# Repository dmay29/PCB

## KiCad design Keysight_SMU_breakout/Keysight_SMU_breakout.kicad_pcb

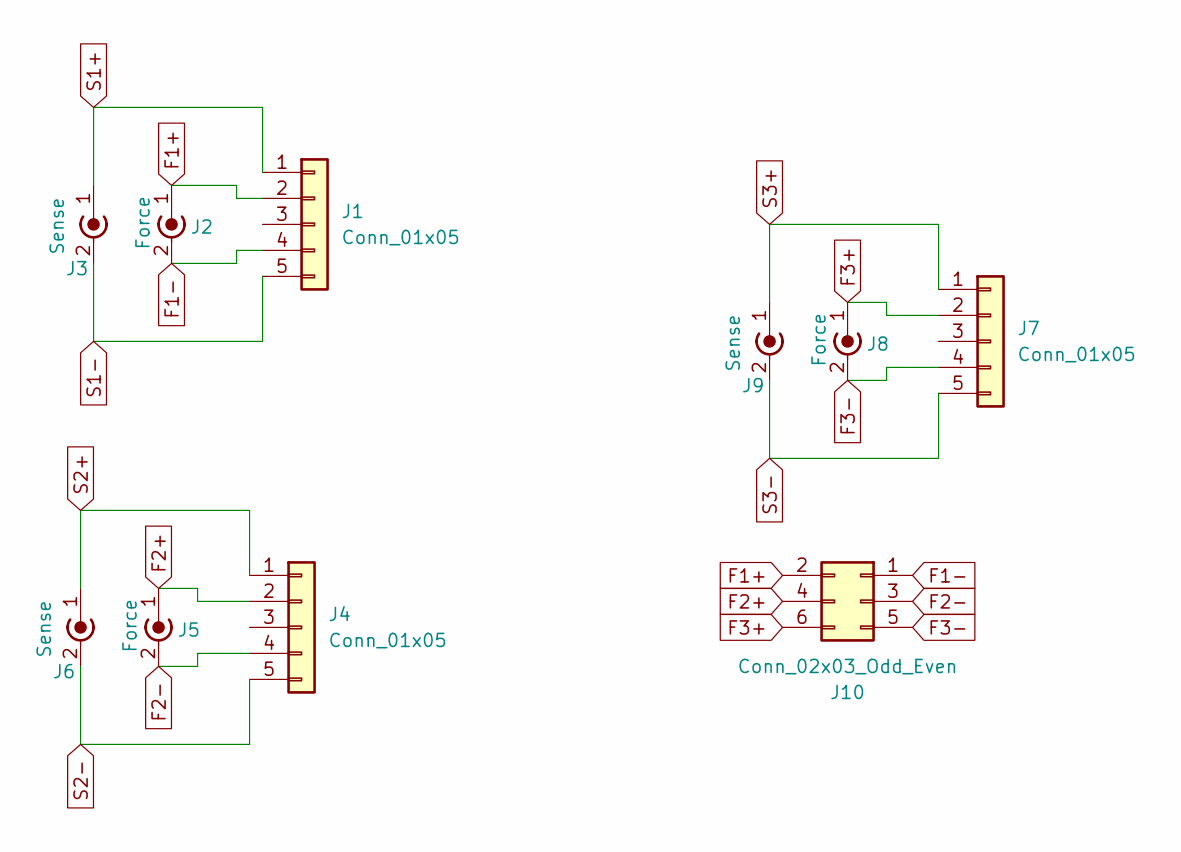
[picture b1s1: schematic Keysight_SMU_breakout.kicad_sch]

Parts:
J1, J4, J7: Conn_01x05; TerminalBlock_Phoenix_MKDS-1-5-3.81_1x05_P3.81mm_Horizontal
J2, J5, J8: Force; BNC_TEConnectivity_1478204_Vertical
J3, J6, J9: Sense; BNC_TEConnectivity_1478204_Vertical
J10: Conn_02x03_Odd_Even; PinHeader_2x03_P2.54mm_Vertical

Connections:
F1+: J1.2, J2.1 (In), J10.2
F1-: J1.4, J2.2 (Ext), J10.1
F2+: J4.2, J5.1 (In), J10.4
F2-: J4.4, J5.2 (Ext), J10.3
F3+: J7.2, J8.1 (In), J10.6
F3-: J7.4, J8.2 (Ext), J10.5
S1+: J1.1, J3.1 (In)
S1-: J1.5, J3.2 (Ext)
S2+: J4.1, J6.1 (In)
S2-: J4.5, J6.2 (Ext)
S3+: J7.1, J9.1 (In)
S3-: J7.5, J9.2 (Ext)

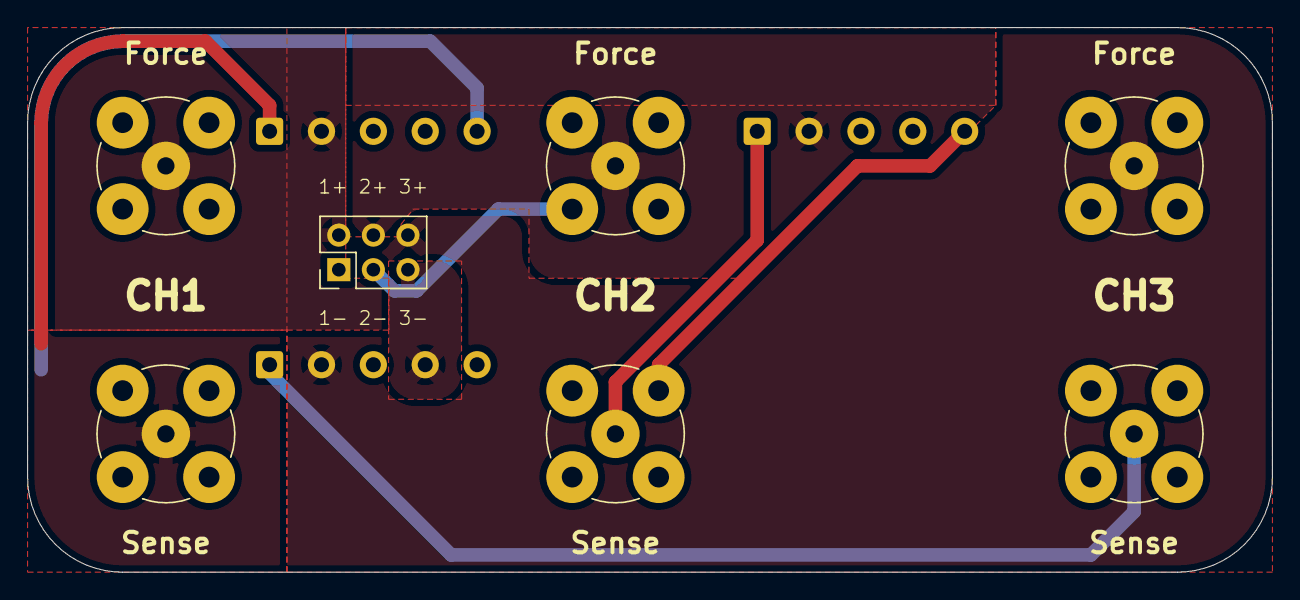
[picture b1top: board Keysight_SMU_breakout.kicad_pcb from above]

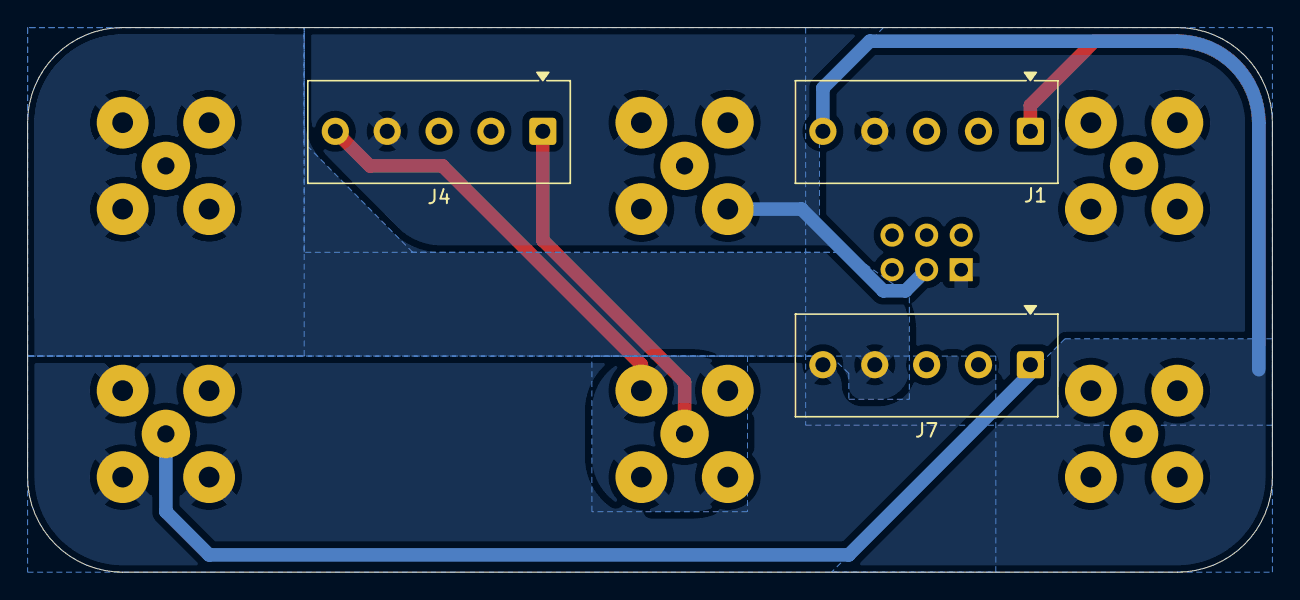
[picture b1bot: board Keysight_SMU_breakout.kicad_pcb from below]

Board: 2 copper layers, 91.4 x 40.0 mm, 10 parts (3 on the bottom side), 12 nets.

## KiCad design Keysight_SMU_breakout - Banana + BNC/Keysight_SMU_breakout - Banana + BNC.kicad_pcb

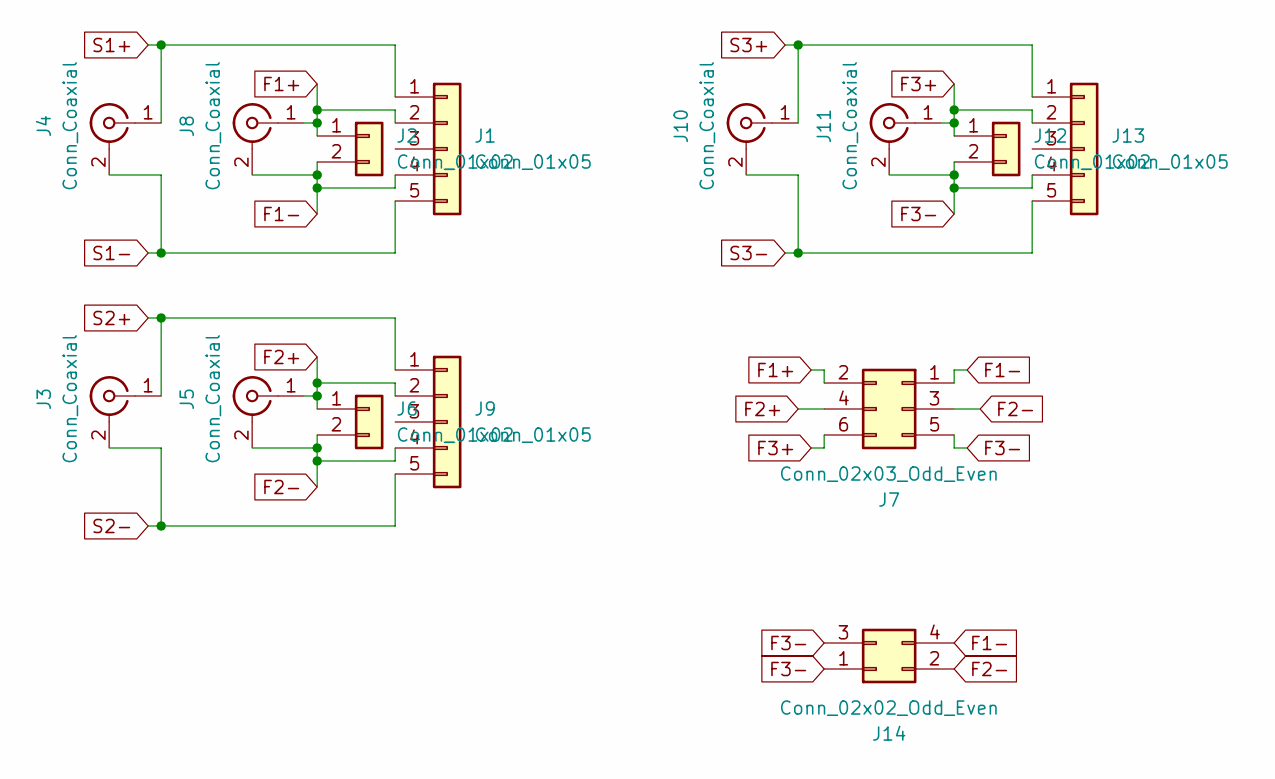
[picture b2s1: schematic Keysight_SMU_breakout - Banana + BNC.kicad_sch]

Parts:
J1, J9, J13: Conn_01x05; TerminalBlock_Phoenix_MKDS-1-5-3.81_1x05_P3.81mm_Horizontal
J2, J6, J12: Conn_01x02; Dual Banana
J3, J4, J5, J8, J10, J11: Conn_Coaxial; BNC_TEConnectivity_1478204_Vertical
J7: Conn_02x03_Odd_Even; PinHeader_2x03_P2.54mm_Vertical
J14: Conn_02x02_Odd_Even; PinHeader_2x02_P2.54mm_Vertical

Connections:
F1+: J1.2, J2.1, J7.2, J8.1 (In)
F1-: J1.4, J2.2, J7.1, J8.2 (Ext), J14.4
F2+: J5.1 (In), J6.1, J7.4, J9.2
F2-: J5.2 (Ext), J6.2, J7.3, J9.4, J14.2
F3+: J7.6, J11.1 (In), J12.1, J13.2
F3-: J7.5, J11.2 (Ext), J12.2, J13.4, J14.1, J14.3
S1+: J1.1, J4.1 (In)
S1-: J1.5, J4.2 (Ext)
S2+: J3.1 (In), J9.1
S2-: J3.2 (Ext), J9.5
S3+: J10.1 (In), J13.1
S3-: J10.2 (Ext), J13.5

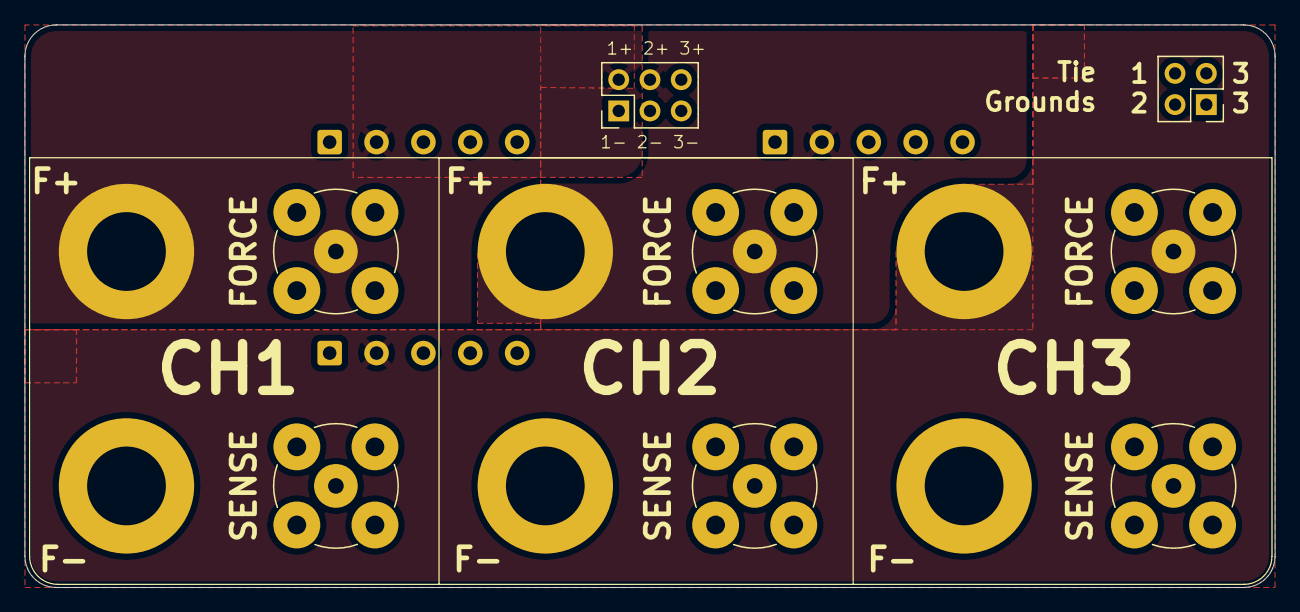
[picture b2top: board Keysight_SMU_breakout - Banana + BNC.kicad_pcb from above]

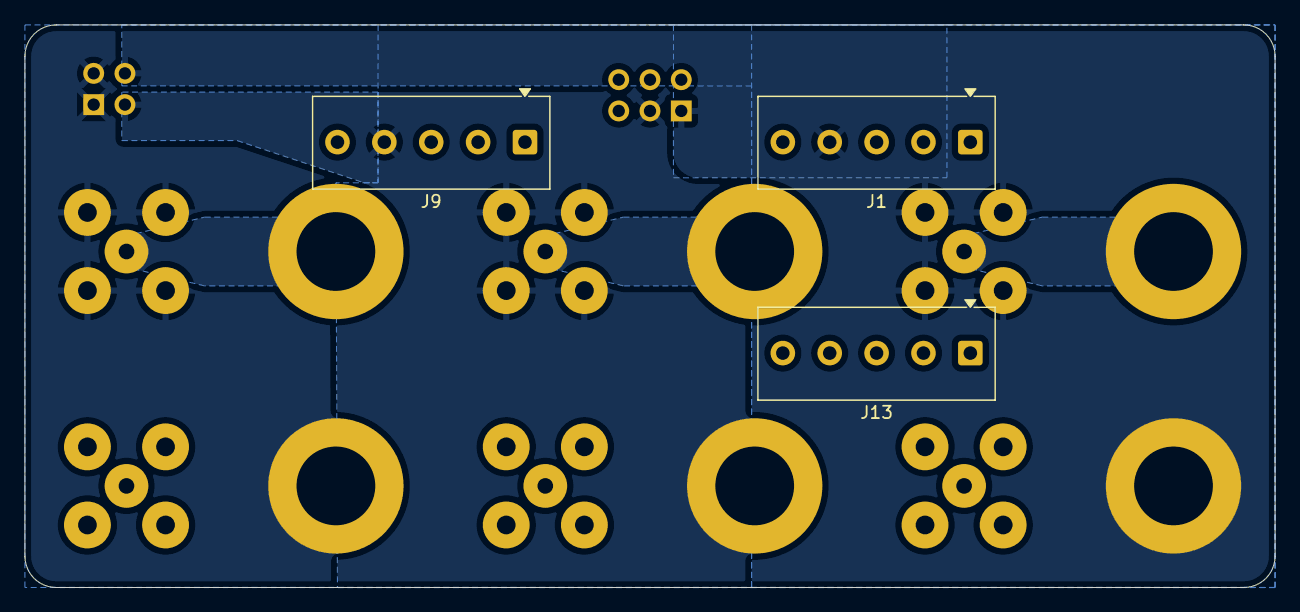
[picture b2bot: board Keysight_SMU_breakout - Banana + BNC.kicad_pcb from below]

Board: 4 copper layers, 101.6 x 45.7 mm, 14 parts (3 on the bottom side), 12 nets.

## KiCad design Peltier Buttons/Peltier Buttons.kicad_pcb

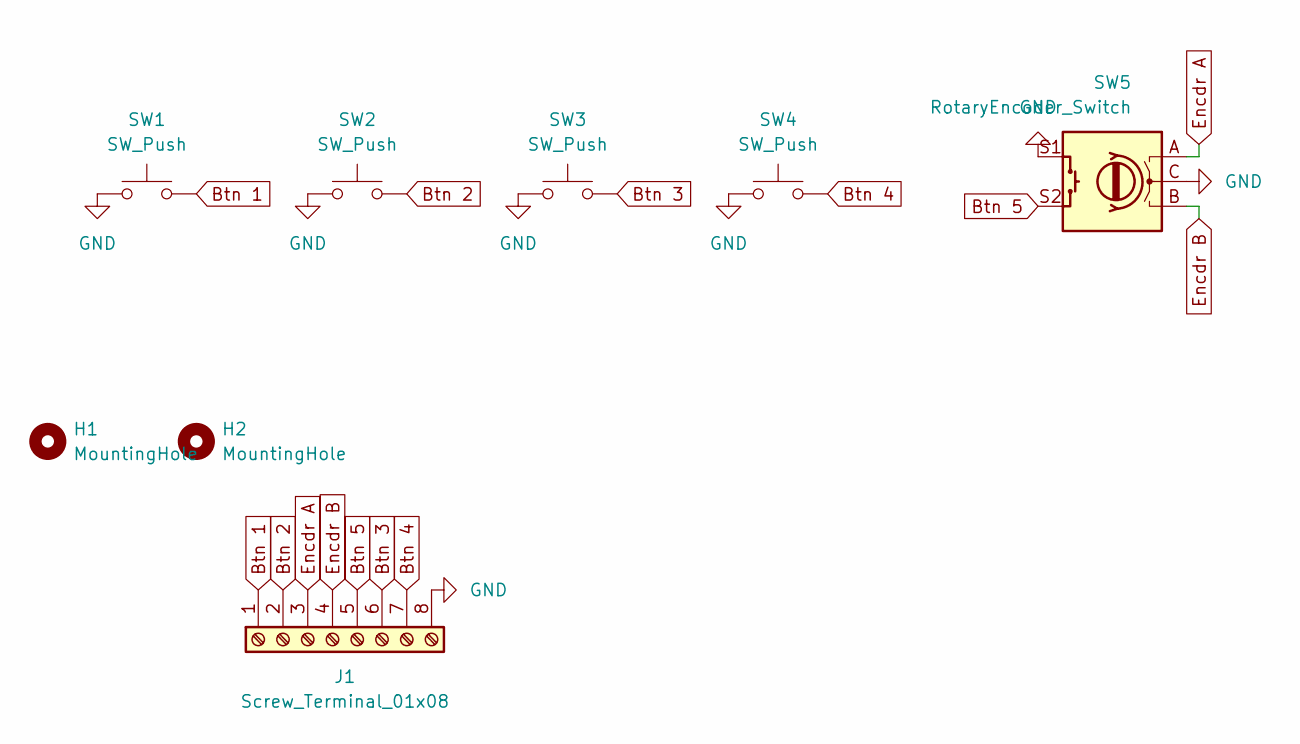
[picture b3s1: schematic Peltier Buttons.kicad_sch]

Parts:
H1, H2: MountingHole; MountingHole_2.7mm_M2.5
J1: Screw_Terminal_01x08; TerminalBlock_TE_282834-8_1x08_P2.54mm_Horizontal
SW1, SW2, SW3, SW4: SW_Push; SW_SPST_Omron_B3F-50xx
SW5: RotaryEncoder_Switch; RotaryEncoder_Bourns_Vertical_PEC12R-3x17F-Sxxxx

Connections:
Btn 1: J1.1, SW1.2
Btn 2: J1.2, SW2.2
Btn 3: J1.6, SW3.2
Btn 4: J1.7, SW4.2
Btn 5: J1.5, SW5.S2
Encdr A: J1.3, SW5.A
Encdr B: J1.4, SW5.B
GND: J1.8, SW1.1, SW2.1, SW3.1, SW4.1, SW5.C, SW5.S1

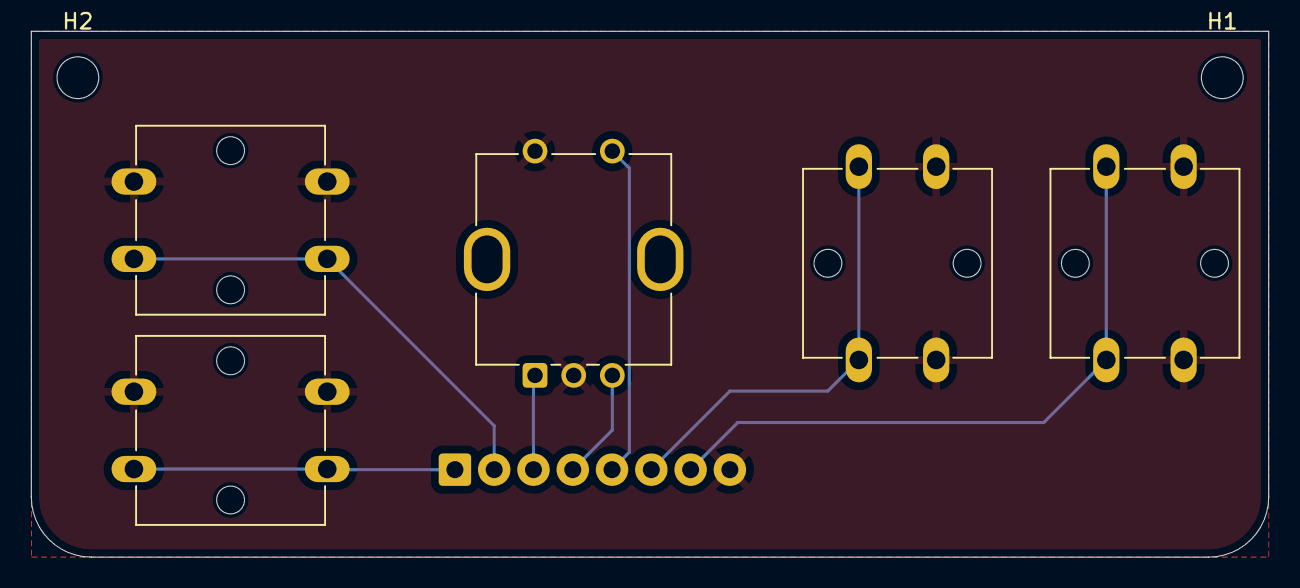
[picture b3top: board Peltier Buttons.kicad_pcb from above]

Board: 2 copper layers, 80.0 x 34.0 mm, 8 parts (1 on the bottom side), 8 nets.

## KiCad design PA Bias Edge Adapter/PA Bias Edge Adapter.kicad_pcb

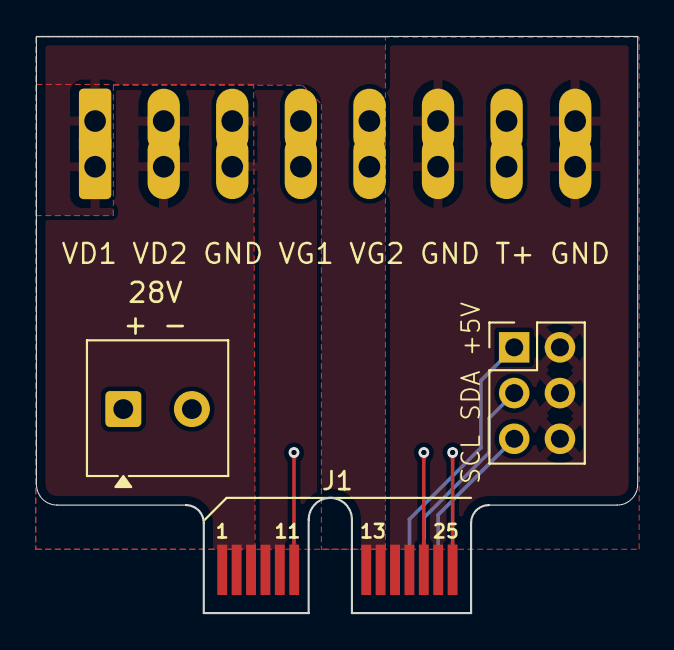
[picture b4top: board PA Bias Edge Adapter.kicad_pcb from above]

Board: 4 copper layers, 33.3 x 32.0 mm, 4 parts (1 on the bottom side), 10 nets.

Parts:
J1: Conn_02x13_Odd_Even; Samtec_HSEC8-113-X-X-DV_2x13_P0.8mm_Wing_Edge
J2: Screw_Terminal_01x08; PhoenixContact_MC_1,5_8-G-3.81_1x08_P3.81mm_Horizontal_Fema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
J3: Screw_Terminal_01x02; TerminalBlock_Phoenix_MKDS-1-2-3.81_1x02_P3.81mm_Horizontal
J4: Conn_02x03_Odd_Even; PinHeader_2x03_P2.54mm_Vertical

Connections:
+5V: J1.20, J4.1
/28V: J1.2, J1.4, J1.6, J1.8, J3.1
/T+: J1.25, J2.7
/VD1: J1.13, J1.15, J2.1
/VD2: J1.1, J1.3, J1.5, J2.2
/VG1: J1.21, J2.4
/VG2: J1.11, J2.5
GND: J1.7, J1.9, J1.10, J1.12, J1.14, J1.16, J1.17, J1.18, J1.19, J1.23, J1.26, J2.3, J2.6, J2.8, J3.2, J4.2, J4.4, J4.6
SCL: J1.24, J4.5
SDA: J1.22, J4.3

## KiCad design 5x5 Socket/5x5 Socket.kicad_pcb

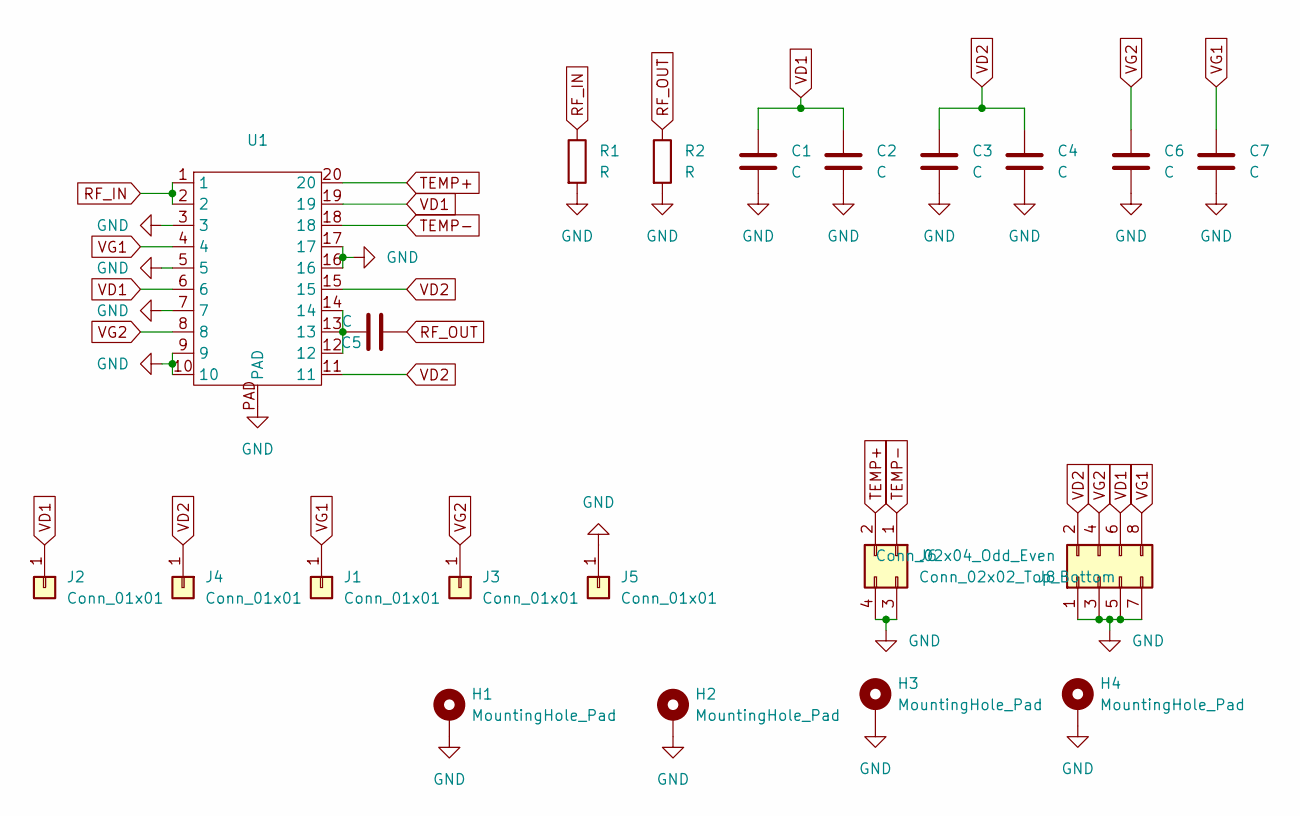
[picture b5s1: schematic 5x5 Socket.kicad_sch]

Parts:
C1, C2, C3, C4, C5, C6, C7: C; C_0603_1608Metric_Pad1.08x0.95mm_HandSolder
H1, H2, H3, H4: MountingHole_Pad; MountingHole_3.2mm_M3_Pad_Via
J1, J2, J3, J4, J5: Conn_01x01; Banana_Cliff_FCR7350Y_S16N-PC_Horizontal
J6: Conn_02x02_Top_Bottom; PinHeader_2x02_P2.54mm_Vertical
J8: Conn_02x04_Odd_Even; PinHeader_2x04_P2.54mm_Vertical
R1, R2: R; R_0603_1608Metric_Pad0.98x0.95mm_HandSolder
U1: 5x5 QFN Socket

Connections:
GND: C1.2, C2.2, C3.2, C4.2, C6.2, C7.2, H1.1, H2.1, H3.1, H4.1, J5.1, J6.3, J6.4, J8.1, J8.3, J8.5, J8.7, R1.2, R2.2, U1.3, U1.5, U1.7, U1.9, U1.10, U1.16, U1.17, U1.PAD
unnamed: C5.1, U1.12, U1.13, U1.14
RF_IN: R1.1, U1.1, U1.2
RF_OUT: C5.2, R2.1
TEMP+: J6.2, U1.20
TEMP-: J6.1, U1.18
VD1: C1.1, C2.1, J2.1, J8.6, U1.6, U1.19
VD2: C3.1, C4.1, J4.1, J8.2, U1.11, U1.15
VG1: C7.1, J1.1, J8.8, U1.4
VG2: C6.1, J3.1, J8.4, U1.8

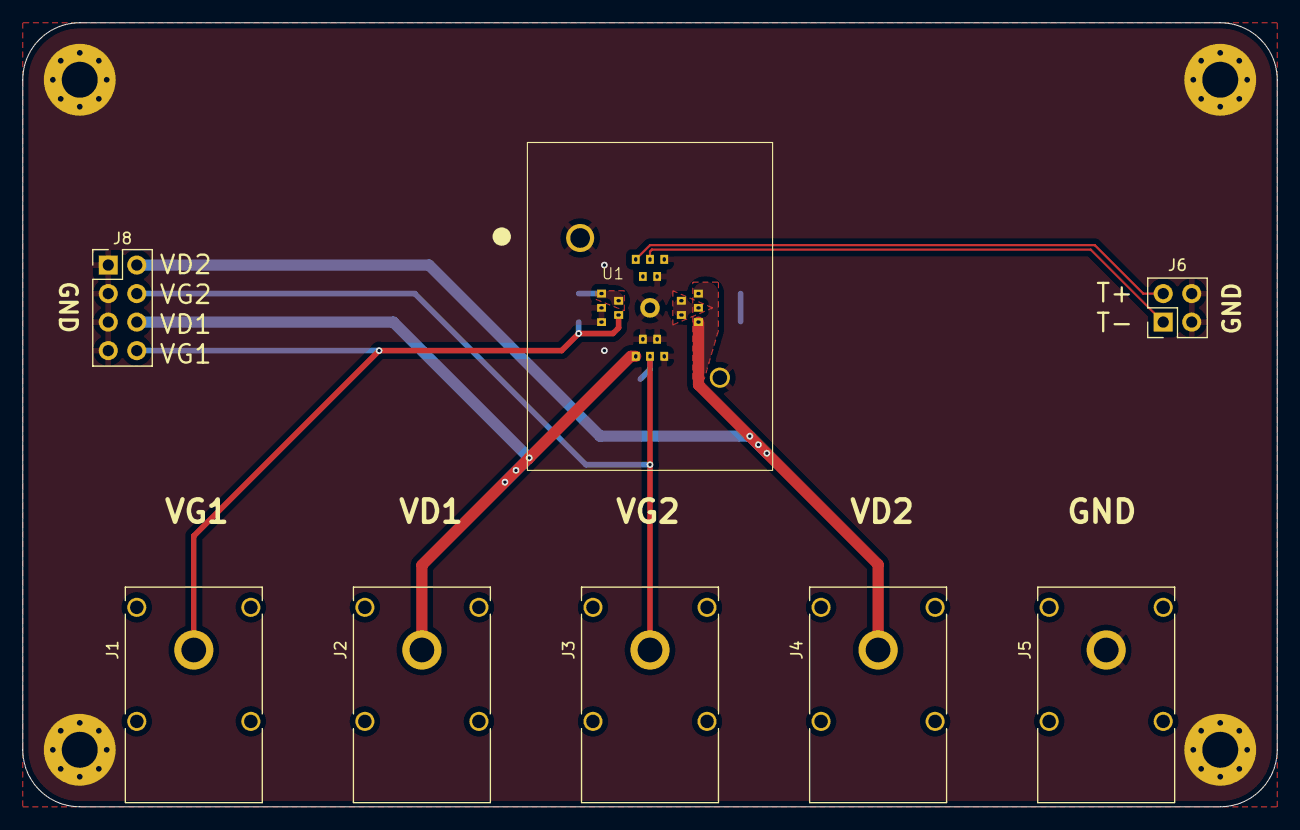
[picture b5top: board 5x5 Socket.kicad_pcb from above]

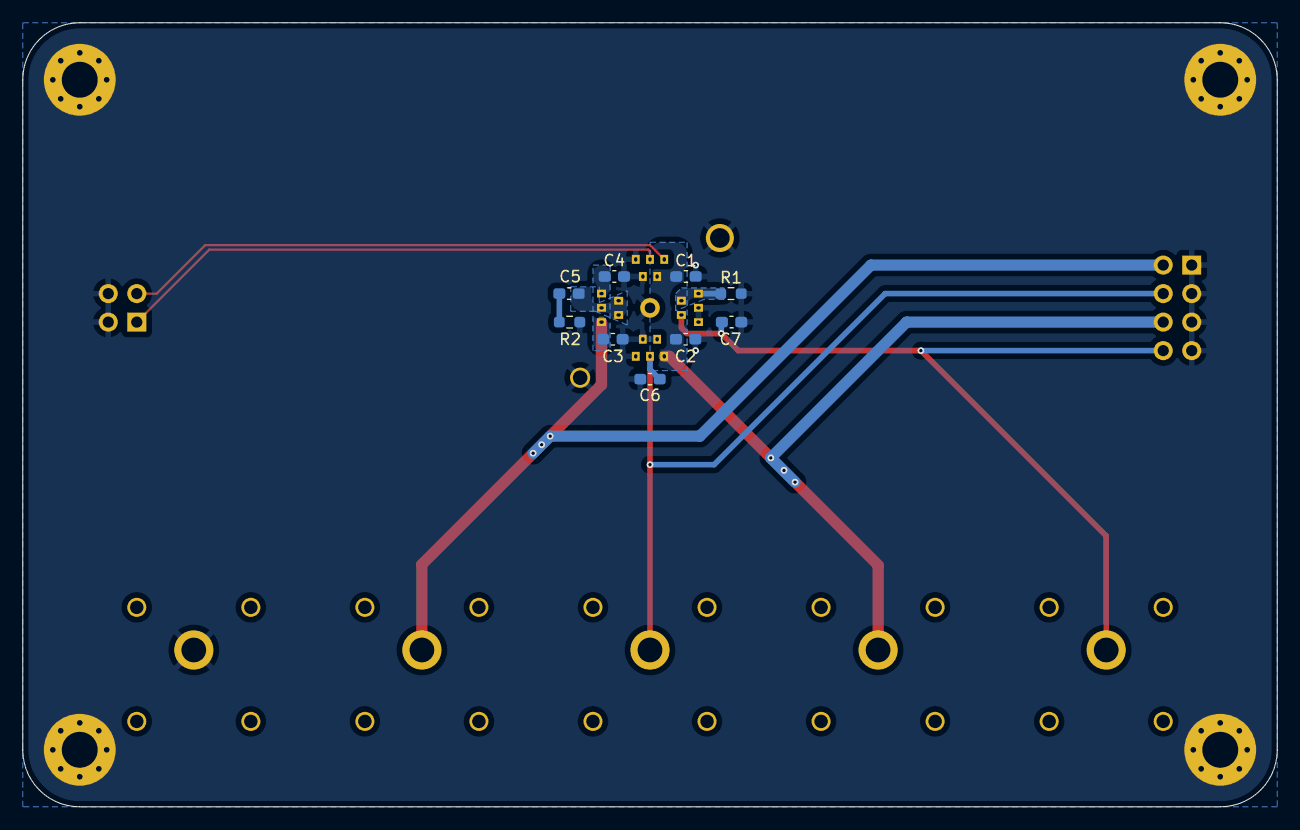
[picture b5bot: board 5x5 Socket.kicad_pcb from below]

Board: 2 copper layers, 111.8 x 69.8 mm, 21 parts (9 on the bottom side), 10 nets.

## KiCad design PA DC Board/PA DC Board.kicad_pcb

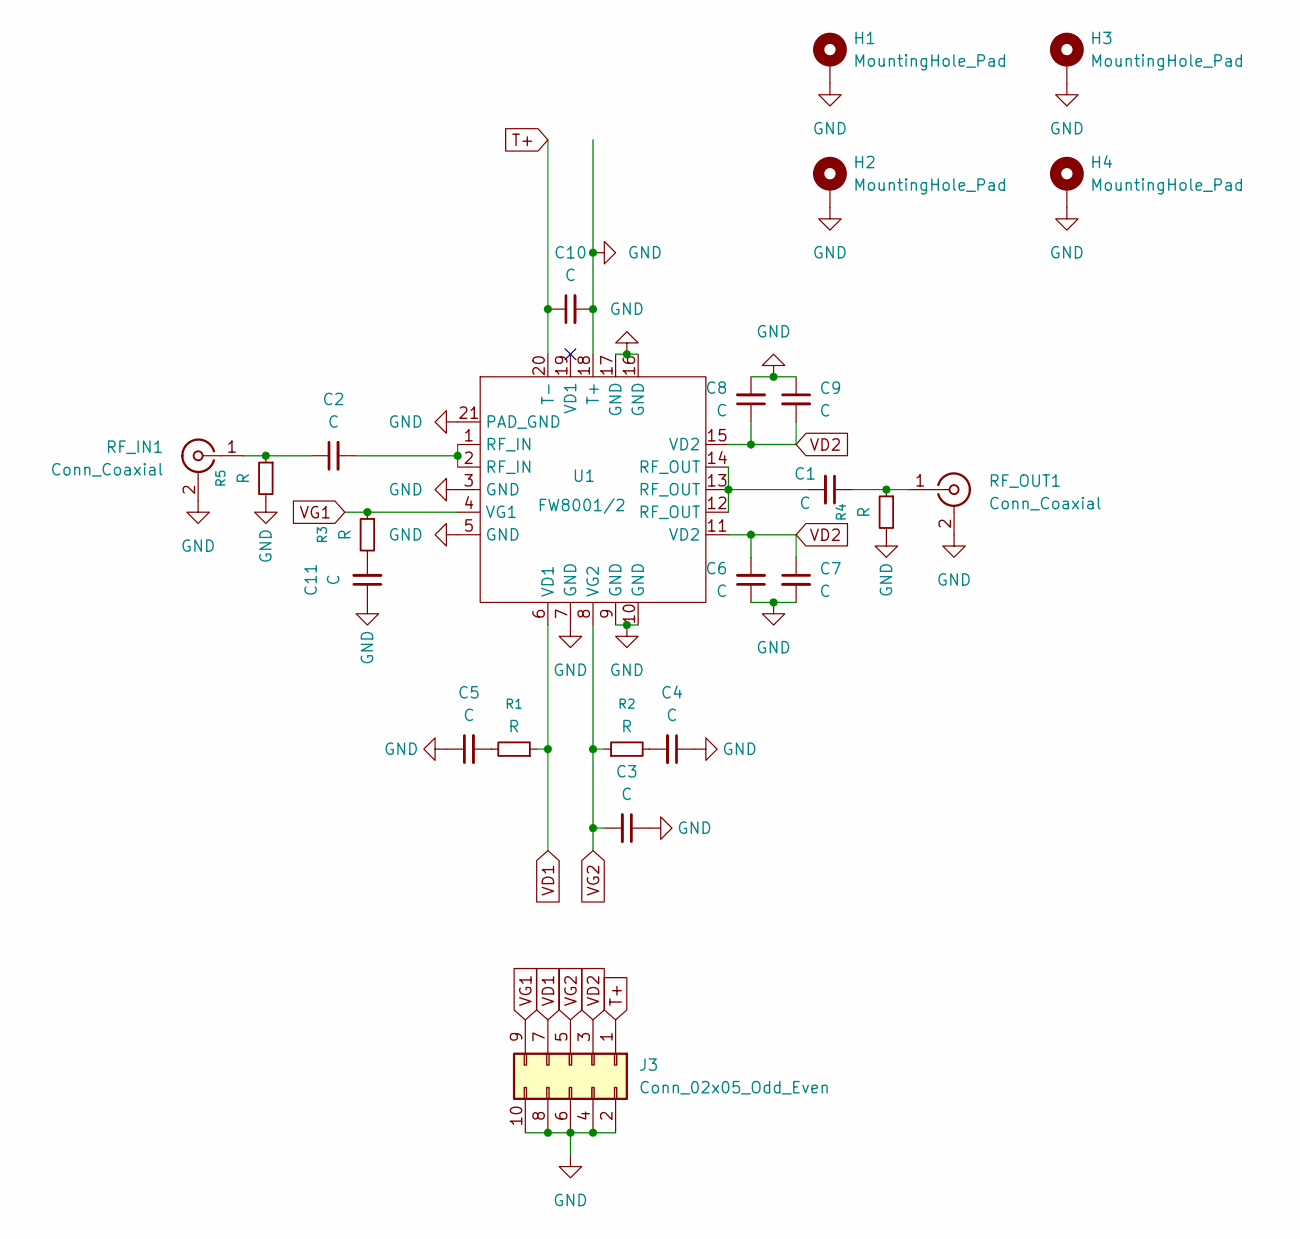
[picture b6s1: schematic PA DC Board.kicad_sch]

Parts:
C1, C2, C3, C4, C5, C10, C11: C; C_0603_1608Metric
C6, C7, C8, C9: C; C_1210_3225Metric
H1, H2, H3, H4: MountingHole_Pad; MountingHole_2.7mm_M2.5_DIN965_Pad_TopBottom
J3: Conn_02x05_Odd_Even; PinHeader_2x05_P2.54mm_Vertical_SMD
R1, R2, R3, R4, R5: R; R_0603_1608Metric
RF_IN1: Conn_Coaxial; SMA_Amphenol_132134-10_Vertical
RF_OUT1: Conn_Coaxial; SMA_Amphenol_132134-10_Vertical
U1: FW8001/2; QFN-20-1EP_5x5mm_P0.65mm_EP3.35x3.35mm

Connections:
GND: C3.1, C4.1, C5.1, C6.1, C7.2, C8.2, C9.1, C10.2, C11.1, H1.1, H2.1, H3.1, H4.1, J3.2, J3.4, J3.6, J3.8, J3.10, R4.2, R5.2, RF_IN1.2 (Ext), RF_OUT1.2 (Ext), U1.3 (GND), U1.5 (GND), U1.7 (GND), U1.9 (GND), U1.10 (GND), U1.16 (GND), U1.17 (GND), U1.18 (T+), U1.21 (PAD_GND)
unnamed: C1.2, U1.12 (RF_OUT), U1.13 (RF_OUT), U1.14 (RF_OUT)
unnamed: C2.2, U1.1 (RF_IN), U1.2 (RF_IN)
unnamed: C4.2, R2.2
unnamed: C5.2, R1.2
unnamed: C11.2, R3.2
unnamed: C2.1, R5.1, RF_IN1.1 (In)
unnamed: C1.1, R4.1, RF_OUT1.1 (In)
T+: C10.1, J3.1, U1.20 (T-)
VD1: J3.7, R1.1, U1.6 (VD1)
VD2: C6.2, C7.1, C8.1, C9.2, J3.3, U1.11 (VD2), U1.15 (VD2)
VG1: J3.9, R3.1, U1.4 (VG1)
VG2: C3.2, J3.5, R2.1, U1.8 (VG2)

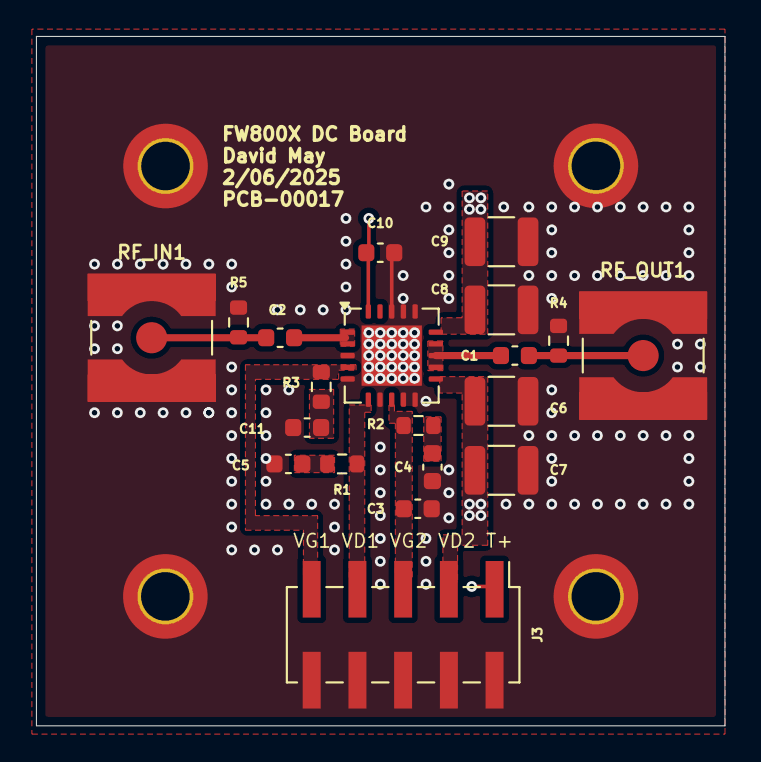
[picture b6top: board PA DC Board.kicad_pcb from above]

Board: 4 copper layers, 38.3 x 38.3 mm, 24 parts (0 on the bottom side), 13 nets.

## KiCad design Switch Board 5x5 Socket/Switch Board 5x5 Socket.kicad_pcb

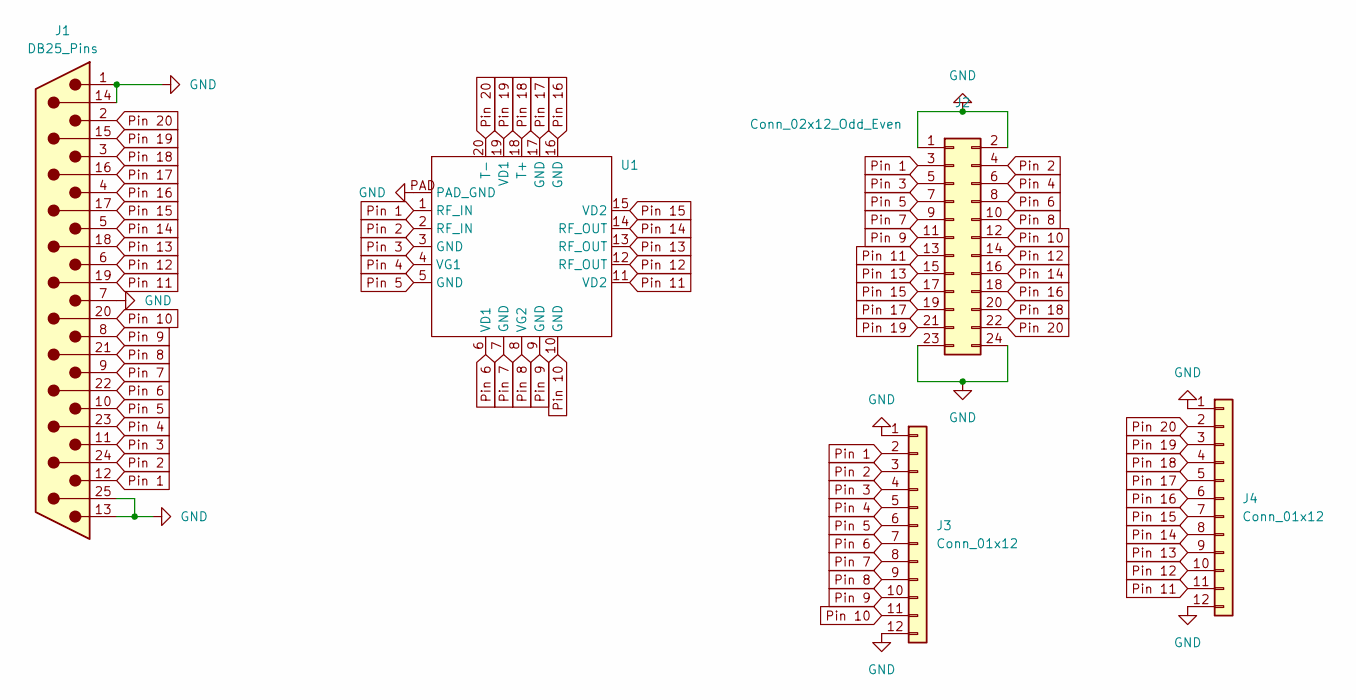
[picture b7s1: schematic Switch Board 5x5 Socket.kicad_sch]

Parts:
J1: DB25_Pins; DSUB-25_Pins_Horizontal_P2.77x2.84mm_EdgePinOffset7.70mm_Ho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
J2: Conn_02x12_Odd_Even; PinHeader_2x12_P2.54mm_Vertical
J3, J4: Conn_01x12; PinHeader_1x12_P2.54mm_Vertical
U1: 5x5 QFN Socket

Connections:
GND: J1.1, J1.7, J1.13, J1.14, J1.25, J2.1, J2.2, J2.23, J2.24, J3.1, J3.12, J4.1, J4.12, U1.PAD (PAD_GND)
Pin 1: J1.12, J2.3, J3.2, U1.1 (RF_IN)
Pin 2: J1.24, J2.4, J3.3, U1.2 (RF_IN)
Pin 3: J1.11, J2.5, J3.4, U1.3 (GND)
Pin 4: J1.23, J2.6, J3.5, U1.4 (VG1)
Pin 5: J1.10, J2.7, J3.6, U1.5 (GND)
Pin 6: J1.22, J2.8, J3.7, U1.6 (VD1)
Pin 7: J1.9, J2.9, J3.8, U1.7 (GND)
Pin 8: J1.21, J2.10, J3.9, U1.8 (VG2)
Pin 9: J1.8, J2.11, J3.10, U1.9 (GND)
Pin 10: J1.20, J2.12, J3.11, U1.10 (GND)
Pin 11: J1.19, J2.13, J4.11, U1.11 (VD2)
Pin 12: J1.6, J2.14, J4.10, U1.12 (RF_OUT)
Pin 13: J1.18, J2.15, J4.9, U1.13 (RF_OUT)
Pin 14: J1.5, J2.16, J4.8, U1.14 (RF_OUT)
Pin 15: J1.17, J2.17, J4.7, U1.15 (VD2)
Pin 16: J1.4, J2.18, J4.6, U1.16 (GND)
Pin 17: J1.16, J2.19, J4.5, U1.17 (GND)
Pin 18: J1.3, J2.20, J4.4, U1.18 (T+)
Pin 19: J1.15, J2.21, J4.3, U1.19 (VD1)
Pin 20: J1.2, J2.22, J4.2, U1.20 (T-)

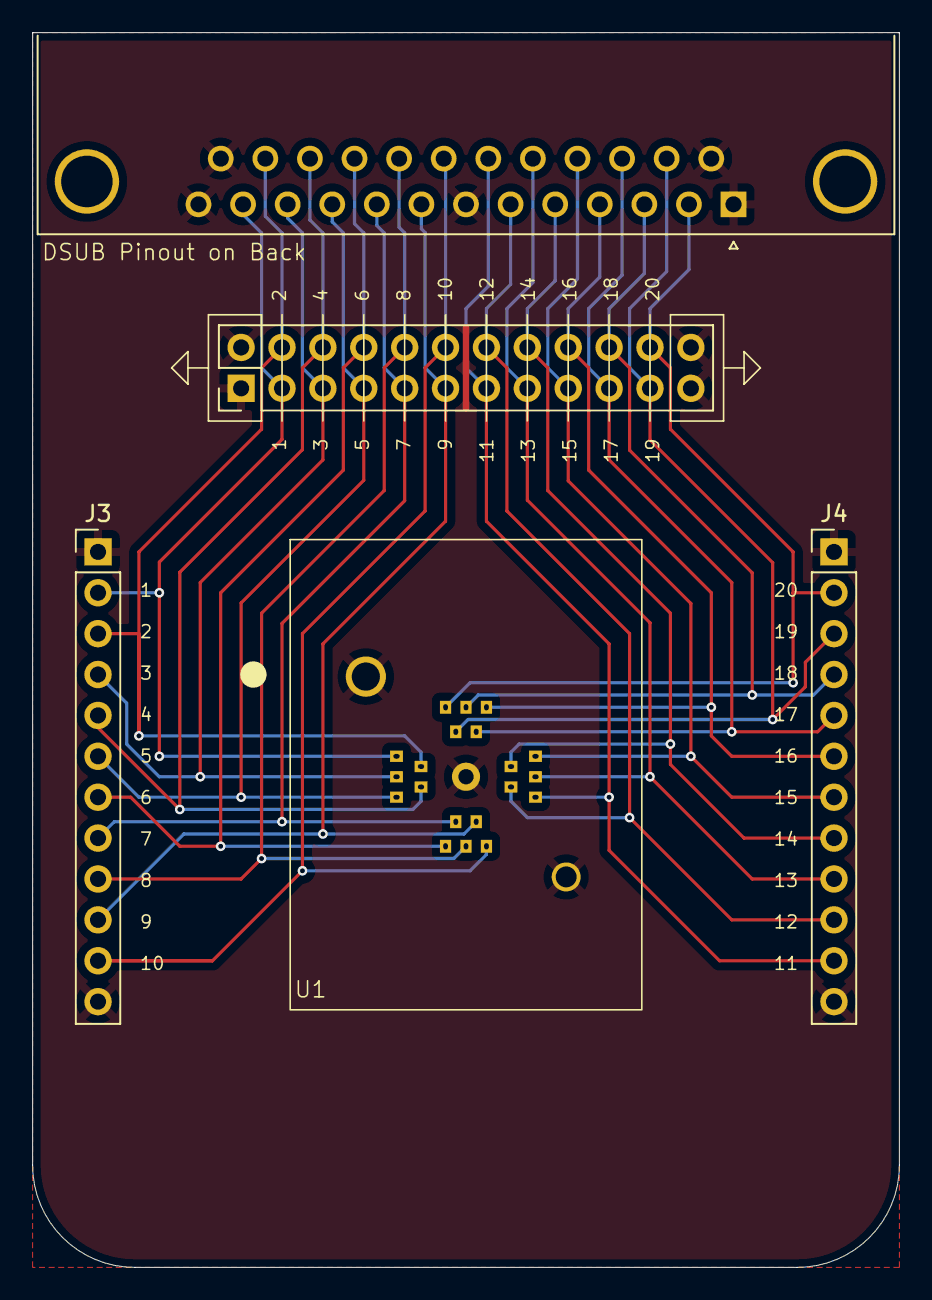
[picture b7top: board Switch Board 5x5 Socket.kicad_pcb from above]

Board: 2 copper layers, 53.8 x 76.7 mm, 5 parts (0 on the bottom side), 21 nets.

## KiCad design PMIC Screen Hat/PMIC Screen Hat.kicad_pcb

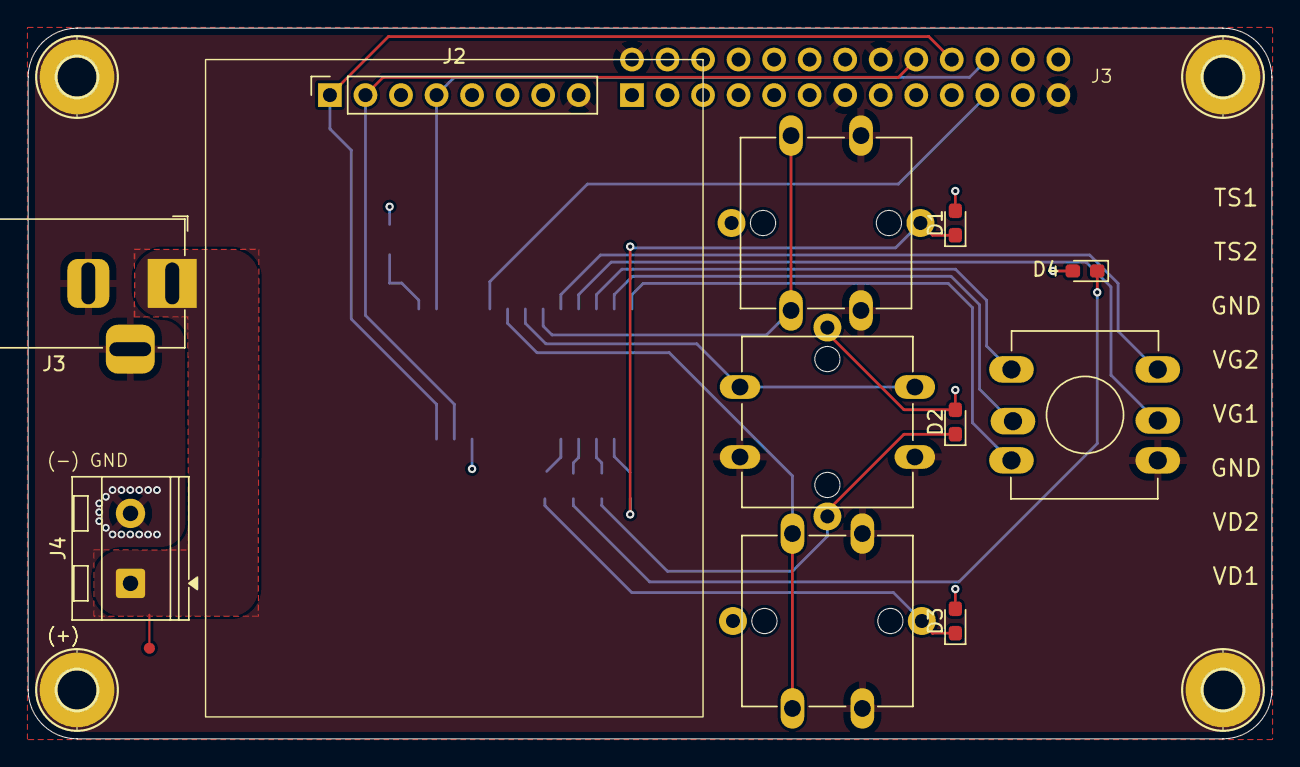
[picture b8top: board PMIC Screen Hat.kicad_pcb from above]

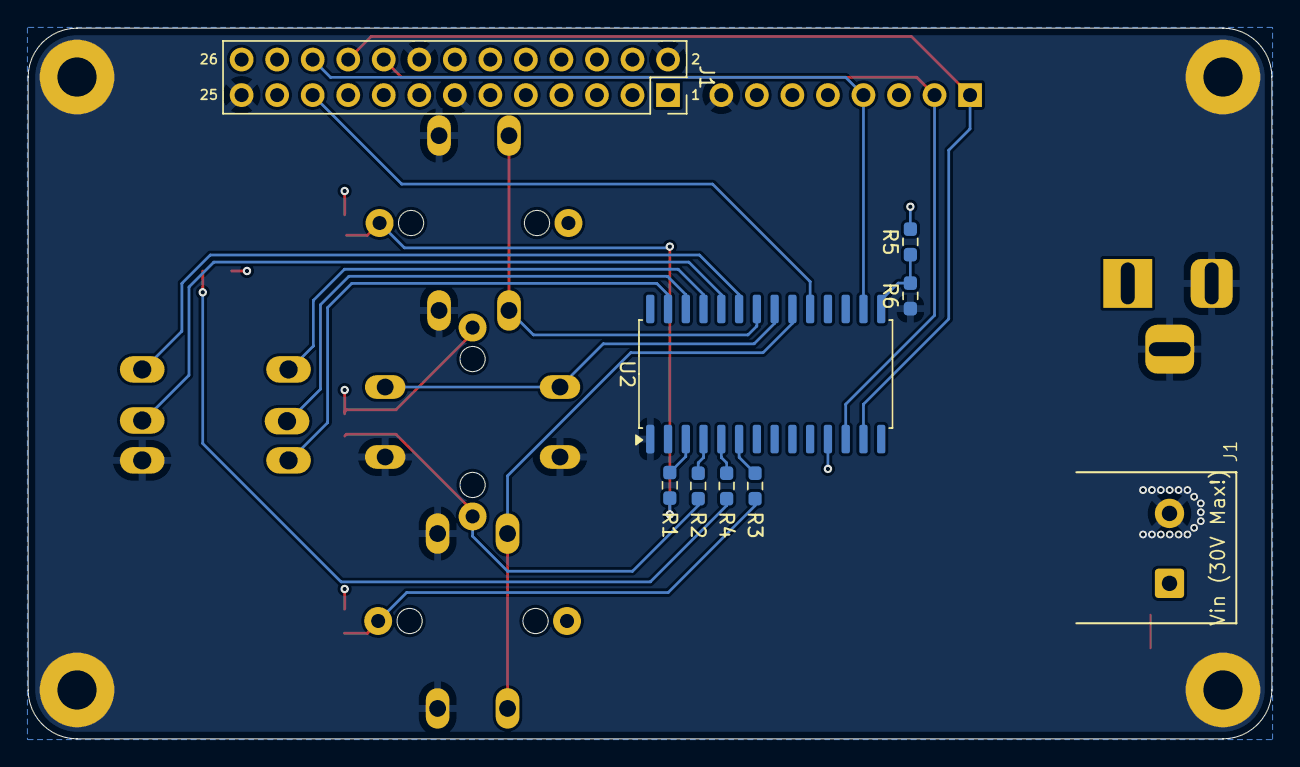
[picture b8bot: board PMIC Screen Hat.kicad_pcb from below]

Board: 4 copper layers, 88.9 x 50.8 mm, 24 parts (8 on the bottom side), 24 nets.

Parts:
D1, D2, D3, D4: LED; LED_0603_1608Metric_Pad1.05x0.95mm_HandSolder
H1, H2, H3, H4: MOUNT-PAD-ROUND2.8; 2,8-PAD_237
J1: Conn_02x13_Odd_Even; PinSocket_2x13_P2.54mm_Vertical
J2: I2C Display; I2C OLED
J3: Barrel_Jack_Switch; BarrelJack_Horizontal
J4: Screw_Terminal_01x02; TerminalBlock_RND_205-00045_1x02_P5.00mm_Horizontal
R1, R2, R3, R4, R5, R6: R_Small; R_0603_1608Metric_Pad0.98x0.95mm_HandSolder
SW1, SW2, SW3: SW_Push_LED; SW_SPST_w_LED_TSD1265
SW9: 5 Way Joystick; 5 Way Joystick - SKQUCAA010
TP1: TPTP08R; TP08R_385
U2: MCP23018x-x-SO; SOIC-28W_7.5x17.9mm_P1.27mm

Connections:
+5V: D1.2 (A), D2.2 (A), D3.2 (A), D4.2 (A), J1.15, J2.7, R5.2, SW1.4 (A), SW2.4 (A), SW3.4 (A), U2.11 (V_{DD})
+28V: J3.1, J4.1, TP1.TP
Down Btn: SW9.3 (Down), U2.27 (GPA7)
Edit LED: R4.2, U2.5 (GPB2)
GND: H1.B2,8, H2.B2,8, H3.B2,8, H4.B2,8, J1.2, J1.13, J1.16, J1.25, J2.8, J3.2, J3.3, J4.2, R6.1, SW1.1, SW2.1, SW3.1, SW9.4 (GND), U2.1 (V_{SS})
INT: J1.21, U2.19 (INTA)
Left Btn: SW9.2 (Left), U2.26 (GPA6)
Middle Btn: SW9.6 (Center), U2.23 (GPA3)
unnamed: D1.1 (K), R1.2, SW1.3 (K)
unnamed: D2.1 (K), R2.2, SW2.3 (K)
unnamed: D3.1 (K), R3.2, SW3.3 (K)
unnamed: D4.1 (K), R4.1
unnamed: R5.1, R6.2, U2.15 (ADDR)
PA Btn: SW2.2, U2.21 (GPA1)
PA LED: R2.1, U2.4 (GPB1)
RST: J1.22, J2.4, U2.16 (~RESET)
Right Btn: SW9.5 (Right), U2.24 (GPA4)
SCL: J1.18, J2.2, U2.12 (SCL)
SDA: J1.20, J2.1, U2.13 (SDA)
Servo Btn: SW3.2, U2.20 (GPA0)
Servo LED: R3.1, U2.6 (GPB3)
Up Btn: SW9.1 (Up), U2.25 (GPA5)
VDD Btn: SW1.2, U2.22 (GPA2)
VDD LED: R1.1, U2.3 (GPB0)

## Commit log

2026-03-20 intial commit
